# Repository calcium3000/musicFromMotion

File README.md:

# musicFromMotion
Convert your slick grooves into sweet tunes.  Body movements are transmitted wirelessly to a host computer and then translated into pre-programmed beats and instruments.  And everything is reconfigurable on the fly; you can serenade or offend the airwaves however you please.

See https://calcium3000.wordpress.com/projects/mfm for more information on the project.

## Hardware
### mFM-Rx
This is the receiver module with which all transmitter nodes communicate.  It consists of a small breakout board for a mini nRF24L01+ transceiver module that plugs directly into the SPI0 bus of a Raspberry Pi (all models).

This module is used in conjunction with TMRh20's RF24 library (see https://github.com/TMRh20/RF24).

### mFM-Tx
Behold the transmitter modules -- the lustrous face of mFM.  Each module consists of a battery, a voltage regulator, a radio transceiver, an accelerometer, and a microcontroller.

When the Rx node pings a Tx node, it reads it accelerometer value and battery status (good or low), sends it back to the Rx node, and takes a quick nap while the other nodes are being pinged.  If the battery voltage is too low the module will sleep until the battery is recharged.

**Note: this version is currently in progress and untested.  Use at your own risk!  And if you do and have any comments or suggestions, please share!**

### License
mFM hardware is licensed under the TAPR Open Hardware License.  See http://tapr.org/ohl.html or LICENSE.txt for full details of the license agreement.

## Software
This section is currently under construction -- i.e. I need to get everything pretty enough to share on the interwebs.  But behold the list of eventual components:
- Tx firmware (Arduino)
- Rx program (C++)
- Rx UDP configurator GUI (optional, Python)
- Main audio program (Pure Data)

### License
All software is licensed under the GNU Public License (GPL) version 3.  See https://www.gnu.org/licenses or COPYING.txt for full details of the license agreement.

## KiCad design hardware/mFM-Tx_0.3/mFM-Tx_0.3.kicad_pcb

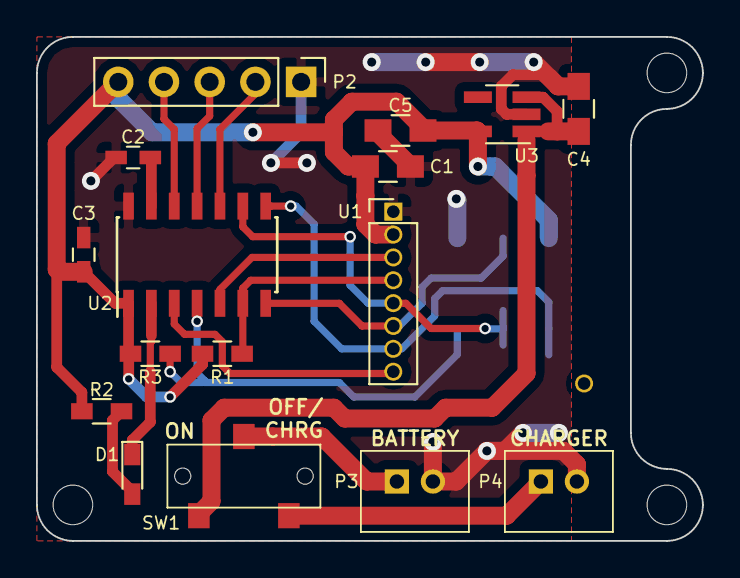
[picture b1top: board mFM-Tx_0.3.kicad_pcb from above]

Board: 2 copper layers, 37.0 x 28.0 mm, 20 parts (1 on the bottom side), 18 nets.

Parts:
C1, C4, C5: 4.7uF; C_0805_HandSoldering
C2, C3: 0.1uF; C_0603_HandSoldering
D1: Blue_LED; LED_0603_HandSoldering
MH0, MH1, MH2: MountingHole_2.2mm_M2_ISO7380
P1: Header_2x3; Socket_Strip_Straight_2x03_Pitch2.54mm_SMD
P2: Header_1x5; ADXL335_header
P3, P4: Header_1x2; B2B-PH-K-S
R1, R3: 10k; R_0603_HandSoldering
R2: 1k; R_0603_HandSoldering
SW1: SPDT; CL-SB-12B-11T
U1: nRF24L01+_module; nRF24L01p_mini_header
U2: ATtiny441-SSU; SOIC-14_3.9x8.7mm_Pitch1.27mm
U3: MIC5205-3.0; SOT-23-5_HandSoldering

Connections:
+BATT: P3.1, SW1.2
+VDD: C1.1, C3.1, C5.1, P1.2, P2.5, R1.1, R2.1, R3.1, U1.2, U2.1, U3.5
/LED_A: D1.2, R2.2
/TINY_AREF: C2.1, U2.13
ACC_X: P2.4, U2.12
ACC_Y: P2.3, U2.11
ACC_Z: P2.2, U2.10
CHRG_VBATT: P4.1, SW1.3
GND: C1.2, C2.2, C3.2, C4.2, C5.2, P1.6, P2.1, P3.2, P4.2, U1.1, U2.14, U3.2
LDO_VBATT: C4.1, SW1.1, U3.1, U3.3
LED_K: D1.1, U2.2
NRF_CE: U1.3, U2.5
NRF_~CS~: R1.2, U1.4, U2.6
NRF_~IRQ~: U1.8, U2.3
SPI_MISO: P1.1, U1.7, U2.8
SPI_MOSI: P1.4, U1.6, U2.7
SPI_SCK: P1.3, U1.5, U2.9
TINY_~RST~: P1.5, R3.2, U2.4

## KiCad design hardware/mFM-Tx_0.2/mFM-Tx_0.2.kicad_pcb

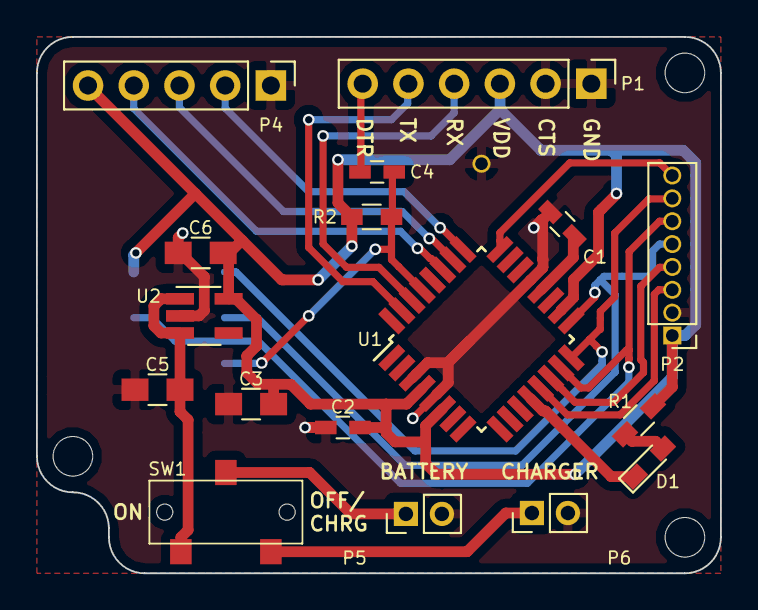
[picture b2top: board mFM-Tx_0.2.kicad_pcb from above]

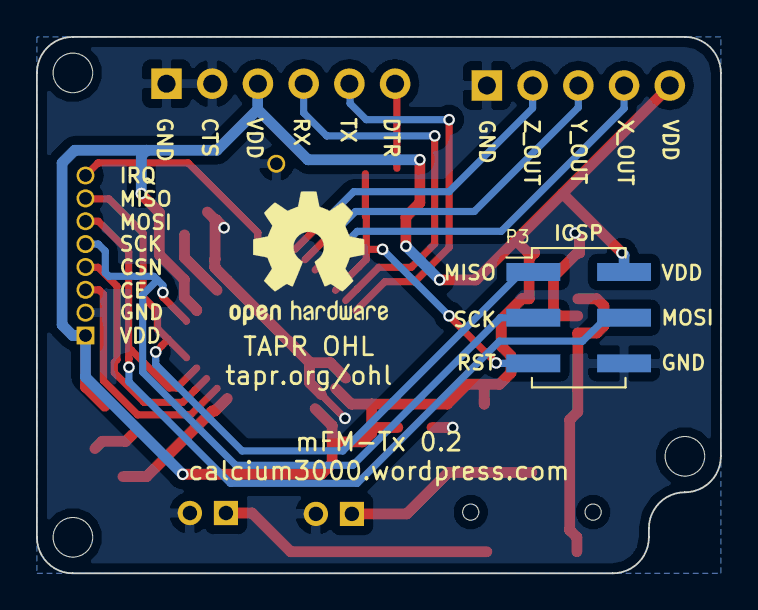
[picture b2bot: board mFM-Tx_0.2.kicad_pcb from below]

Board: 2 copper layers, 38.0 x 29.8 mm, 22 parts (2 on the bottom side), 21 nets.

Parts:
C1, C2, C4: 0.1uF; C_0603_HandSoldering
C3, C5, C6: 4.7uF; C_0805_HandSoldering
D1: Blue_LED; LED_0603_HandSoldering
MH0, MH6, MH7: MountingHole_2.2mm_M2_ISO7380
P1: Header_1x6; Socket_Strip_Straight_1x06_Pitch2.54mm
P2: Header_1x9; nRF24L01p_mini_header
P3: Header_2x3; Socket_Strip_Straight_2x03_Pitch2.54mm_SMD
P4: Header_1x5; ADXL335_header
P5, P6: Header_1x2; B2B-PH-K-S
R1: 1k; R_0603_HandSoldering
R2: 10k; R_0603_HandSoldering
SW1: SPDT; SW_SPDT_SMD
SYM0: OSHW-Logo2_9.8x8mm_SilkScreen
U1: ATmega368P-AU; TQFP-32_7x7mm_Pitch0.8mm
U2: MIC5205-3.3; SOT-23-5_HandSoldering

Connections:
+BATT: P5.1, SW1.2
+VDD: C2.1, C3.1, C6.1, P1.3, P2.1, P3.2, P4.5, R1.1, R2.1, U1.4, U1.6, U1.18, U2.5
/LED_A: D1.2, R1.2
/MC_AREF: C1.1, U1.20
ACC_X: P4.4, U1.27
ACC_Y: P4.3, U1.26
ACC_Z: P4.2, U1.25
CHRG_VBATT: P6.1, SW1.3
GND: C1.2, C2.2, C3.2, C5.2, C6.2, P1.1, P1.2, P2.2, P2.9, P3.6, P4.1, P5.2, P6.2, U1.3, U1.5, U1.21, U2.2
LDO_VBATT: C5.1, SW1.1, U2.1, U2.3
LED_K: D1.1, U1.12
NRF_CE: P2.3, U1.13
NRF_CSN: P2.4, U1.14
NRF_IRQ: P2.8, U1.24
PROG_DTR: C4.2, P1.6
PROG_RST: C4.1, P3.5, R2.2, U1.29
PROG_RX: P1.4, U1.30
PROG_TX: P1.5, U1.31
SPI_MISO: P2.7, P3.1, U1.16
SPI_MOSI: P2.6, P3.4, U1.15
SPI_SCK: P2.5, P3.3, U1.17

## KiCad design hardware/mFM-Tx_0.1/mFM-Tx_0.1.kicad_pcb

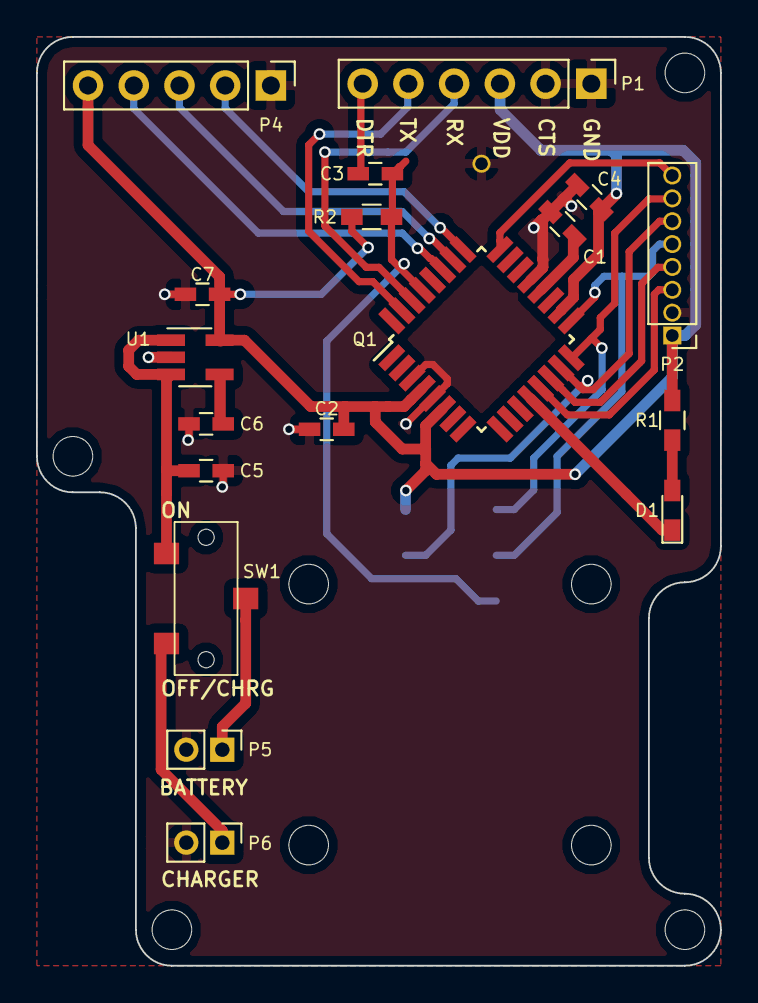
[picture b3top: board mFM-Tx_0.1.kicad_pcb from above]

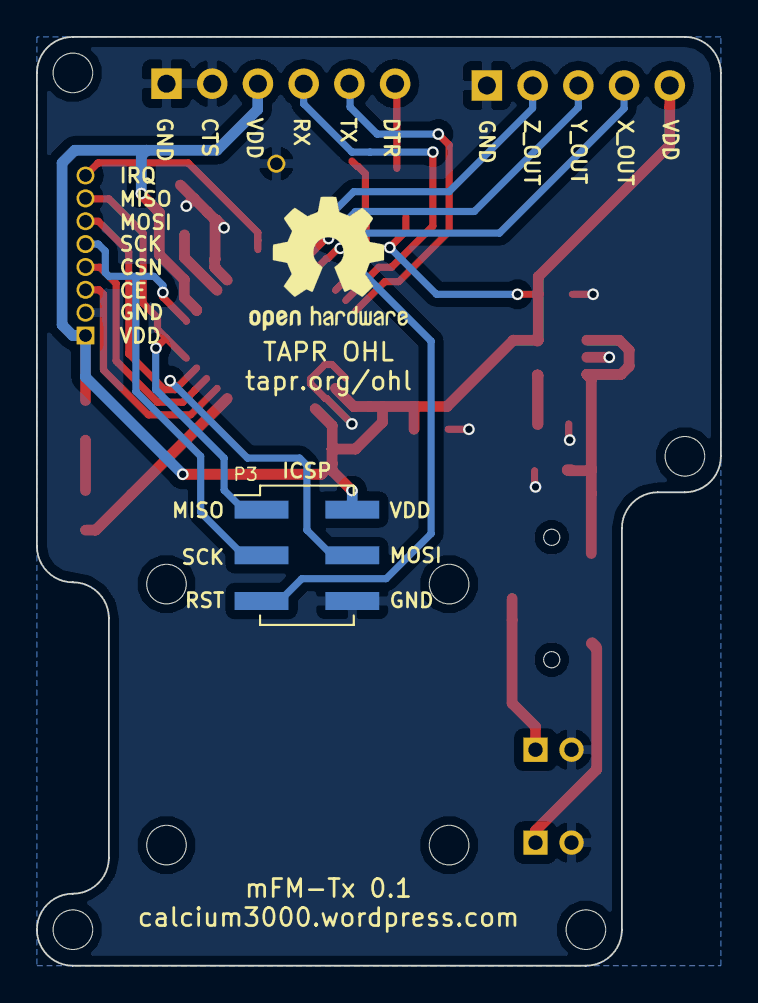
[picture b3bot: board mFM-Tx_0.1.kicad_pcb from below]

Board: 2 copper layers, 38.0 x 51.6 mm, 28 parts (2 on the bottom side), 22 nets.

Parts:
C1, C2, C3: 0.1uF; C_0603_HandSoldering
C4, C5, C7: 1uF; C_0603_HandSoldering
C6: 470pF; C_0603_HandSoldering
D1: Blue_LED; LED_0603_HandSoldering
MH0, MH1, MH2, MH3, MH4, MH5, MH6, MH7: MountingHole_2.2mm_M2_ISO7380
P1: Header_1x6; Socket_Strip_Straight_1x06_Pitch2.54mm
P2: Header_1x9; nRF24L01p_mini_header
P3: Header_2x3; Socket_Strip_Straight_2x03_Pitch2.54mm_SMD
P4: Header_1x5; ADXL335_header
P5, P6: Header_1x2; Socket_Strip_Straight_1x02_Pitch2.00mm
Q1: ATmega368P-AU; TQFP-32_7x7mm_Pitch0.8mm
R1: 1k; R_0603_HandSoldering
R2: 10k; R_0603_HandSoldering
SW1: SPDT; SW_SPDT_SMD
SYM0: OSHW-Logo2_9.8x8mm_SilkScreen
U1: TC1015-2.8V; SOT-23-5_HandSoldering

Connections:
+BATT: P5.1, SW1.2
+VDD: C2.1, C4.1, C7.1, P1.3, P2.1, P3.2, P4.5, Q1.4, Q1.6, Q1.18, R1.1, R2.1, U1.5
/LDO_BYP: C6.1, U1.4
/LED_A: D1.2, R1.2
/MC_AREF: C1.1, Q1.20
ACC_X: P4.4, Q1.27
ACC_Y: P4.3, Q1.26
ACC_Z: P4.2, Q1.25
CHRG_VBATT: P6.1, SW1.3
GND: C1.2, C2.2, C4.2, C5.2, C6.2, C7.2, P1.1, P1.2, P2.2, P2.9, P3.6, P4.1, P5.2, P6.2, Q1.3, Q1.5, Q1.21, U1.2
LDO_VBATT: C5.1, SW1.1, U1.1, U1.3
LED_K: D1.1, Q1.12
NRF_CE: P2.3, Q1.13
NRF_CSN: P2.4, Q1.14
NRF_IRQ: P2.8, Q1.24
PROG_DTR: C3.2, P1.6
PROG_RST: C3.1, P3.5, Q1.29, R2.2
PROG_RX: P1.4, Q1.30
PROG_TX: P1.5, Q1.31
SPI_MISO: P2.7, P3.1, Q1.16
SPI_MOSI: P2.6, P3.4, Q1.15
SPI_SCK: P2.5, P3.3, Q1.17

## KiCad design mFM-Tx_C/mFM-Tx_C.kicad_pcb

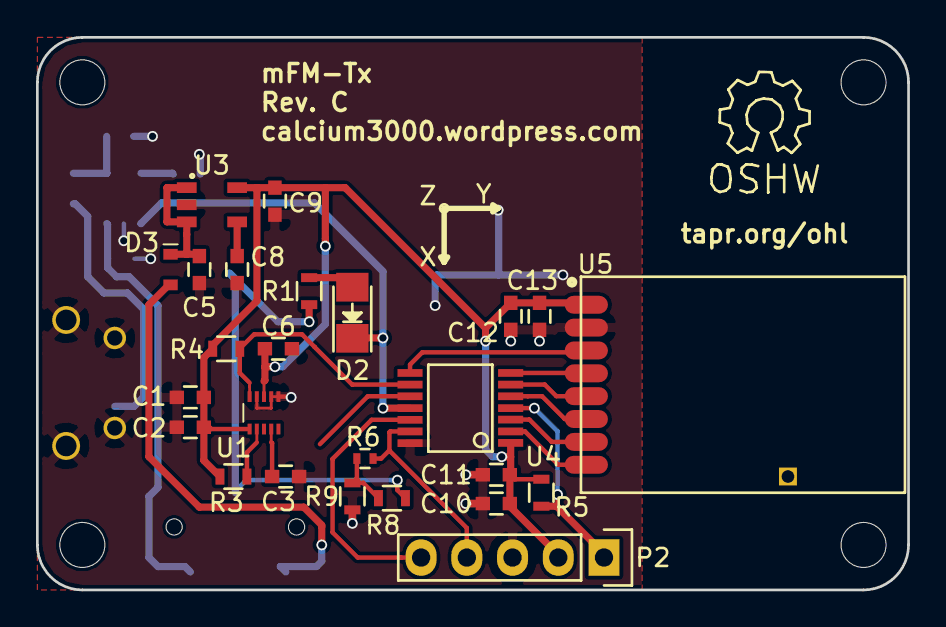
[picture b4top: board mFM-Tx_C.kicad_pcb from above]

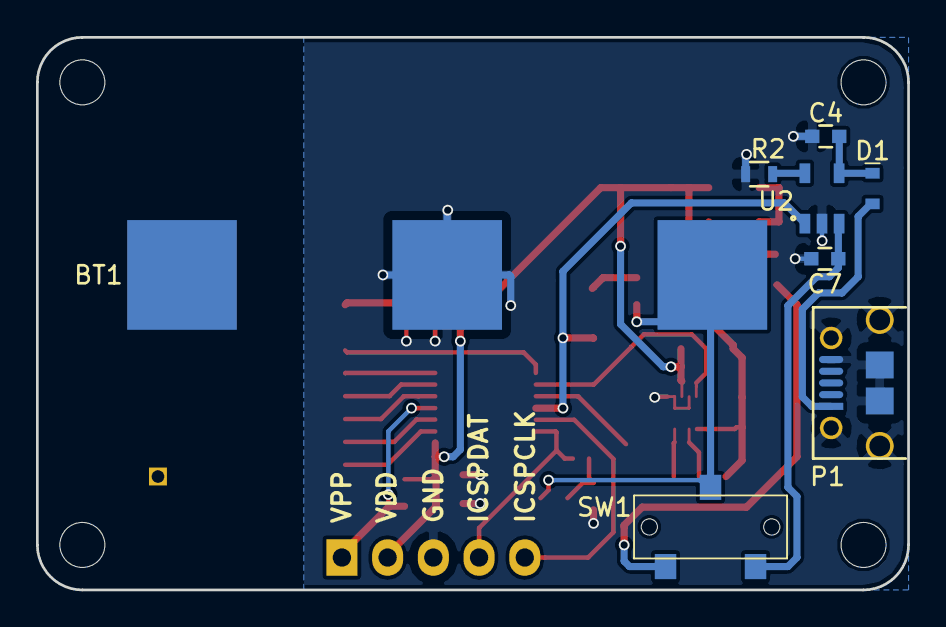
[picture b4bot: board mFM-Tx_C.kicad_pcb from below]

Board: 2 copper layers, 48.4 x 30.7 mm, 39 parts (8 on the bottom side), 25 nets.

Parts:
BT1: LIPO; CR2450_clip
C1, C5, C9, C10: 1uF; C_0603
C2, C3, C6, C11, C13: 0.1uF; C_0603
C4, C7, C12: 4.7uF; C_0603
C8: 470pF; C_0603
D1, D3: DB2S316; SSMini2
D2: LED; LED_1206
LAB0: Symbol_OSHW-Logo_SilkScreen
LAB1: XYZ_ref
MH0, MH1, MH2, MH3: MountingHole_2-5mm
P1: USB_MICRO_B; micro_USB_B
P2: CONN_01X05; Socket_Strip_Straight_1x05
R1, R3, R4: 1k; R_0603
R2, R5, R8, R9: 10k; R_0603
R6: 0; R_0402
SW1: SPDT; SW_SPDT_SMD
U1: MMA8653; DFN-10-2mmx2mm
U2: MCP73832; SOT-23-5
U3: TC1015-2.8V; SOT-23-5
U4: PIC16LF18323_TSSOP; SSOP-14
U5: NRF24L01P_MINI; nRF24L01p_mini

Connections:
+BATT: BT1.1, R1.2, R8.1, SW1.2
/ACC_BYP: C3.1, U1.4
/CHGR_ISET: R2.1, U2.5
/CHGR_VBATT: C7.1, SW1.3, U2.3
/LDO_BYP: C8.1, U3.4
/LDO_VBATT: C5.1, D3.1, U3.1, U3.3
/LDO_VBATT_IN: D3.2, SW1.1
/LED_A: D2.2, R1.1
/PIC_VBATT: R6.1, R8.2, R9.2
/VUSB: C4.1, D1.1, U2.4
CE: U4.8, U5.3
GND: BT1.2, C1.2, C2.2, C3.2, C4.2, C5.2, C6.2, C7.2, C8.2, C9.2, C10.2, C11.2, C12.2, C13.2, P1.5, P1.6, P2.3, R2.2, R9.1, U1.6, U1.7, U1.9, U2.2, U3.2, U4.14, U5.2
ICSPCLK: P2.5, U4.12
ICSPDAT: P2.4, R6.2, U4.13
LED_K: D2.1, U2.1, U4.11
MISO: U4.3, U5.7
MOSI: U4.5, U5.6
SCK: U4.6, U5.5
SCL: R3.2, U1.2, U4.10
SDA: R4.2, U1.10, U4.9
VDD: C1.1, C2.1, C6.1, C9.1, C10.1, C11.1, C12.1, C13.1, P2.2, R3.1, R4.1, R5.2, U1.1, U1.8, U3.5, U4.1, U5.1
VPP: P2.1, R5.1, U4.4
VUSB_IN: D1.2, P1.1
~CSN: U4.7, U5.4
~IRQ: U4.2, U5.8

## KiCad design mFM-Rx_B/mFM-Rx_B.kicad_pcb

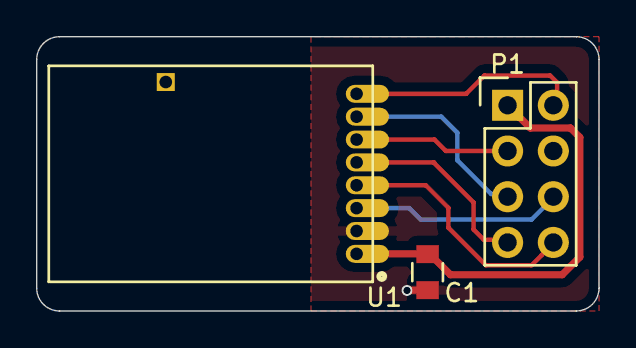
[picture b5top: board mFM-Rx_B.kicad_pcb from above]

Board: 2 copper layers, 31.2 x 15.2 mm, 3 parts (0 on the bottom side), 8 nets.

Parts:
C1: 10uF; C_0805
P1: 02x04; Socket_Strip_Straight_2x04_mirrored
U1: NRF24L01P_MINI; nRF24L01p_mini_TH

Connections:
CE: P1.6, U1.3
GND: C1.2, P1.4, U1.2
MISO: P1.5, U1.7
MOSI: P1.3, U1.6
SCK: P1.7, U1.5
VDD: C1.1, P1.1, U1.1
~CSN: P1.8, U1.4
~IRQ: P1.2, U1.8

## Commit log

2016-07-23 Initial commit of Rx, Tx, and pretty
2016-07-23 First cleanup of backup and unused files
2016-07-23 Second cleanup of backup and unused files
2016-07-23 Added license file
2016-07-29 Updated schematics and PCBs
2016-07-29 Updated Tx PCB
2016-07-30 Created Tx gerbers
2017-05-15 Updated component and footprint libraries, updated mFM-Tx to Rev C, updated mFM-Rx to Rev B
2017-08-28 Created separate folders for hardware and software files
2017-08-28 Added logo
2017-08-28 Added Tx Arduino sketch for node 1 (left hand)
2017-08-28 Updated 'Use' section for Tx1 Arduino sketch
2017-08-29 Added Rx files, moved logo, updated Tx Arduino sketch
2017-09-28 Added Tx hardware files for versions 0.1 and 0.2
2017-09-28 Updated gerbers for Tx_0.1 and _0.2
2017-09-30 Updated VDD to 3.3V on mFM-Tx_0.2
2017-10-15 Upgraded to Tx 0.3, substituted ATtiny441 for ATmega328p, removed serial programming, modified PCB layout
2018-04-11 Updated README for Tx v0.3
2018-04-16 Added part numbers to and cleaned up schematic

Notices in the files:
hardware/mFM-Tx_0.3/mFM-Tx_0.3.kicad_pcb:
Released under the TAPR Open Hardware License >> http://tapr.org/ohl
